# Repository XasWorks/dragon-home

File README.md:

# dragon-home
A rework of our old SmartHome project, this time done cleanly and neatly~

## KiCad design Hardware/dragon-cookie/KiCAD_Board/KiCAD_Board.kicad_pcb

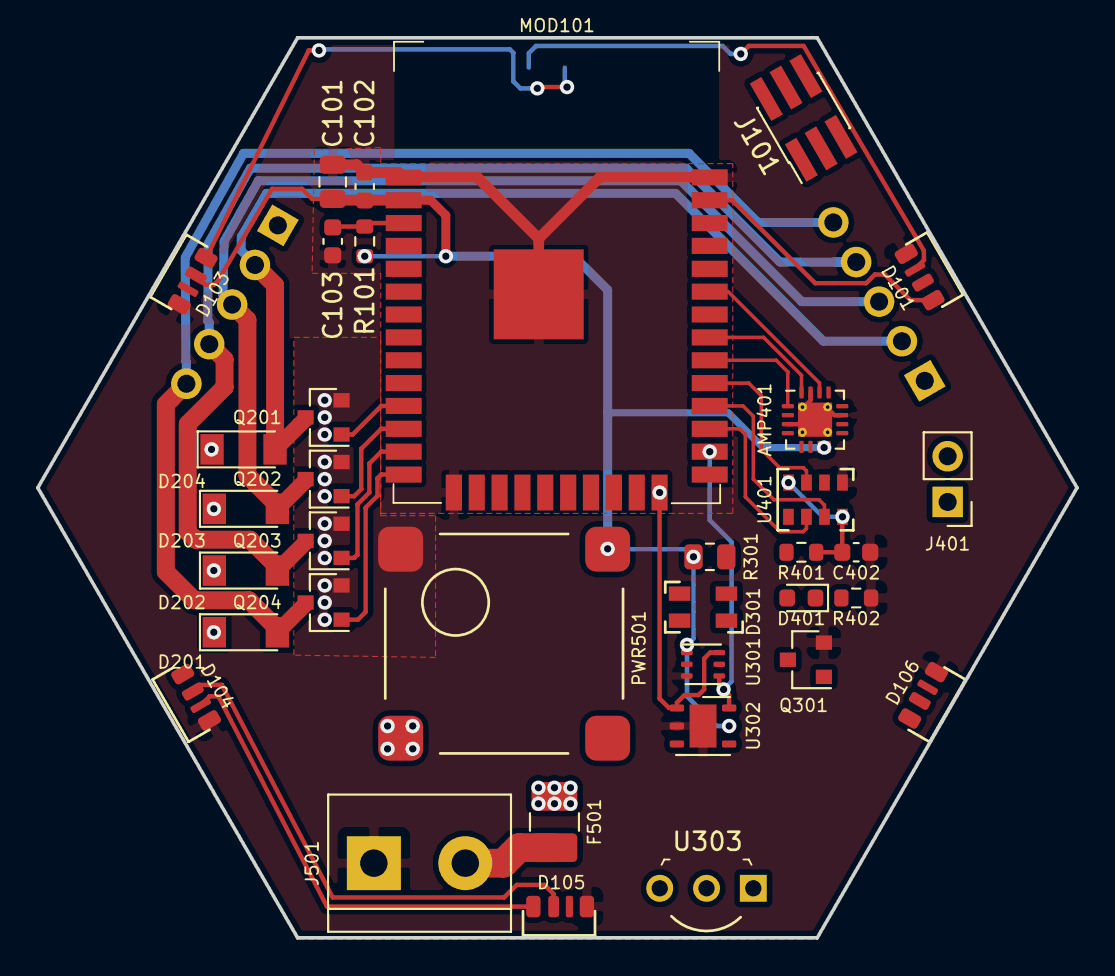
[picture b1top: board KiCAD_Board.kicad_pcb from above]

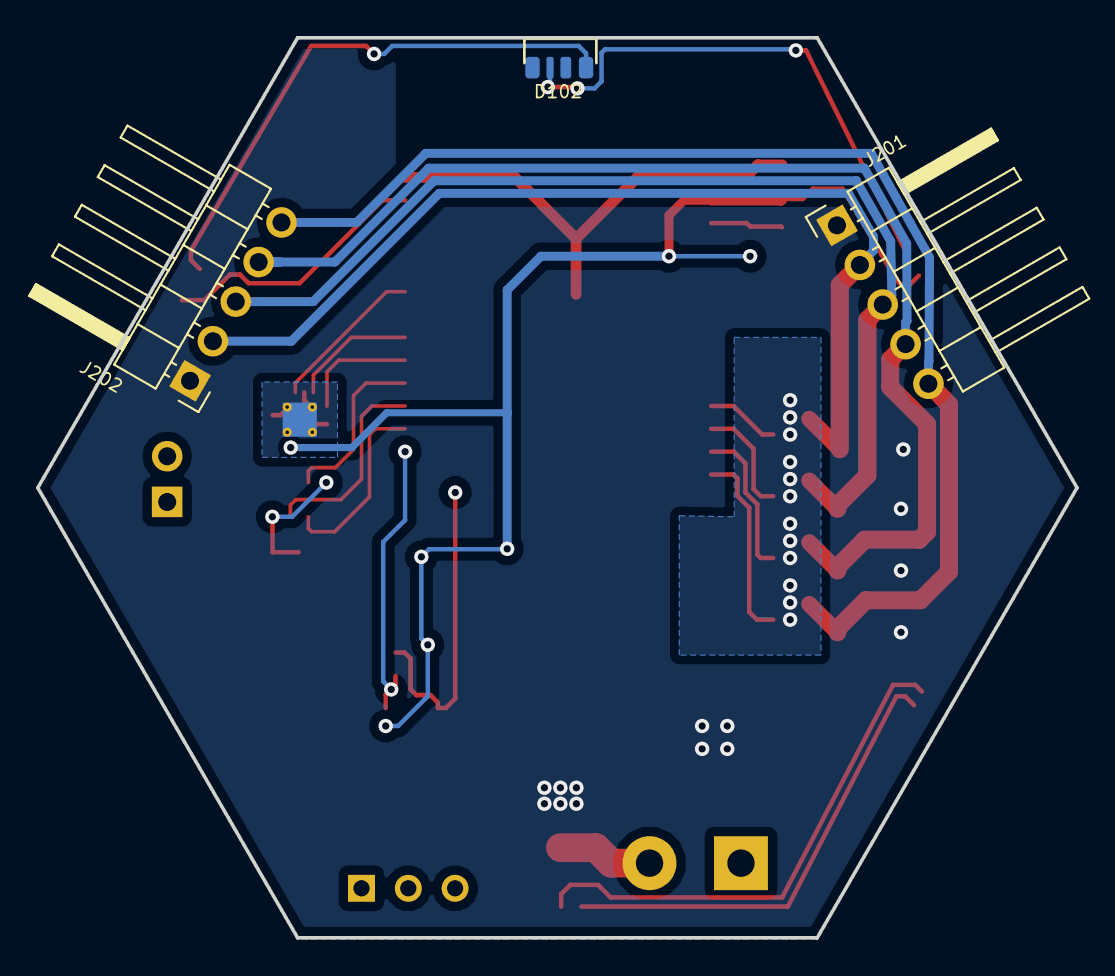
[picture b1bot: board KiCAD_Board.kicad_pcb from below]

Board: 2 copper layers, 57.7 x 50.0 mm, 38 parts (3 on the bottom side), 34 nets.

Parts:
AMP401: MAX98357A; QFN-16-1EP_3x3mm_P0.5mm_EP1.9x1.9mm_ThermalVias
C101: C; C_0805_2012Metric
C102, C103, C402: C_Small; C_0603_1608Metric
D101, D102, D103, D104, D105, D106: IN-PI42TAS
D201, D202, D203, D204: LL4148-GS08; D_MiniMELF
D301: SFH 4240-Z; SFH 4240
D401: LED; LED_0603_1608Metric
F501: Fuse; Fuse_1210_3225Metric_Castellated
J101: Conn_02x03_Odd_Even; PinHeader_2x03_P1.27mm_Vertical_SMD
J201, J202: Conn_01x05; PinHeader_1x05_P2.54mm_Horizontal
J401: Conn_01x02_Female; PinHeader_1x02_P2.54mm_Vertical
J501: Screw_Terminal_01x02; TerminalBlock_bornier-2_P5.08mm
MOD101: ESP32-WROOM-32; ESP32-WROOM-32D
PWR501: ROF-78E3.3-0.5SMD-R; ROF-78E
Q201, Q202, Q203, Q204, Q301: DMN3404L-7; SOT-23
R101, R401, R402: R_Small; R_0603_1608Metric
R301: 12R; R_0805_2012Metric
U301: LTR-303ALS-01; Lite-On_LTR-303ALS-01
U302: Si7020-A20; DFN-6-1EP_3x3mm_P1mm_EP1.5x2.4mm
U303: TSSP58038; TO-92-3_Formed_Leads
U401: CMM-4030

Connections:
+3V3: AMP401.7, AMP401.8, C101.1, C102.1, D101.1, D102.1, D103.1, D104.1, D105.1, D106.1, MOD101.2, PWR501.3, R101.1, R301.1, U301.1, U302.5
+VDC: D201.1, D202.1, D203.1, D204.1, F501.1, J201.1, J202.1, PWR501.1
/RESET: C103.1, MOD101.3, R101.2
AUDIO_RX_BCK: MOD101.27, U401.6
AUDIO_RX_DATA: MOD101.28, U401.7
AUDIO_RX_LR: MOD101.29, U401.3
AUDIO_TX_BCK: AMP401.16, MOD101.31
AUDIO_TX_DATA: AMP401.1, MOD101.30
AUDIO_TX_LR: AMP401.14, MOD101.33
GND: AMP401.3, AMP401.11, AMP401.15, AMP401.17, C101.2, C102.2, C103.2, C402.1, D101.3, D102.3, D103.3, D104.3, D105.3, D106.3, J501.1, MOD101.1, MOD101.15, MOD101.38, MOD101.39, PWR501.2, Q201.2, Q202.2, Q203.2, Q204.2, Q301.2, R402.2, U301.3, U302.2, U302.7, U401.1
I2C_SCL: MOD101.26, U301.4, U302.6
I2C_SDA: MOD101.24, U301.6, U302.1
MIC_3.3V: D401.2, R401.1
unnamed: AMP401.9, J401.1
unnamed: AMP401.10, J401.2
unnamed: C402.2, R401.2, U401.4, U401.8
unnamed: D101.2, D102.4
unnamed: D102.2, D103.4
unnamed: D103.2, D104.4
unnamed: D104.2, D105.4
unnamed: D105.2, D106.4
unnamed: D201.2, J201.5, J202.5, Q204.3
unnamed: D202.2, J201.4, J202.4, Q203.3
unnamed: D203.2, J201.3, J202.3, Q202.3
unnamed: D204.2, J201.2, J202.2, Q201.3
unnamed: D301.1, Q301.3
unnamed: D301.2, R301.2
unnamed: D401.1, R402.1
unnamed: F501.2, J501.2
PWM_B: MOD101.13, Q203.1
PWM_G: MOD101.12, Q202.1
PWM_R: MOD101.11, Q201.1
PWM_WW: MOD101.14, Q204.1
WS2812_OUT: D101.4, MOD101.37

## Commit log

2021-02-09 Add a few necessary footprints
2021-02-09 Start work on the first dragon cookie schematics
2021-02-26 Produce Gerbers for v1.0 of the dragon-cookie hardware
2021-03-07 Continue work on the cookie mount
2021-03-07 Nibble a bit more on the FCSTD Model
2021-03-09 Add basis for programming
2021-03-09 Bump XasCode
2021-03-11 Added SDKConfig
2021-03-17 Add a bunch of stuff
2021-03-17 Update XasCode
2021-03-17 Add updated mount
2021-05-06 Fix the 3D Models
2021-05-06 Do a lot of fancy magic
2021-05-06 Do even more magic, sorry
2021-05-13 Use the improved conversation system and add Telegram
2021-05-13 Improve speech silence parameters
2021-05-18 Add WakeWord detection <3
2021-05-18 Overhaul the conversation module and add a Interface and a Stargate
    Look I'm not that good at comitting at the right times, OK? >.>
2021-06-27 Add the ruby code of the smart home
2021-08-22 ... Y-Yes?
2021-08-22 Update XasCode to track new BLE code
2021-08-26 Add first BLE tests to DragonCookie
2021-08-30 Start tweaking the system to use just a tad less RAM
2021-08-30 Will this track master??
2021-09-09 Work on fixing the glitched OTA
2021-09-15 Continue work on improving NetHelpers
2021-09-28 Add rakefile with versioning system
2024-07-04 Safety commit
2024-07-04 Not even sure what this is
